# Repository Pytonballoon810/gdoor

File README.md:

<div align="center">

# GDoor

**Open hardware and firmware that connect a Gira door intercom to your smart home.**

Ring the doorbell, get a notification. Press a button in Home Assistant, the door opens.

&nbsp;

<sub>Left: the classic adapter (v3.1) &nbsp;·&nbsp; Right: the new DIN-rail board</sub>

</div>

---

## ✨ What it does

GDoor listens to and talks on the two-wire Gira door system bus. It is a DIY alternative to the
Gira TKS-IP-Gateway, built entirely from reverse-engineered findings about the bus.

<table>
<tr>
<td width="50%" valign="top">

### 🔔 Listen
Every bus message arrives in your smart home: doorbell presses, floor calls, the indoor
station picking up. Trigger a phone notification, a chime or a camera snapshot.

</td>
<td width="50%" valign="top">

### 🔓 Send
Put any message on the bus from an automation: open the door, switch the light, call a
station.

</td>
</tr>
<tr>
<td valign="top">

### 🏠 Integrate
[Home Assistant](https://gdoor-org.github.io/documentation/homeassistant.html) and
[openHAB](https://gdoor-org.github.io/documentation/openhab.html) through MQTT, or native
Home Assistant entities through the [ESPHome component](esphome/README.md).

</td>
<td valign="top">

### 🎙️ Talk *(in development)*
Two-way voice from the door station to Home Assistant over VoIP, on the boards with the
ES8374 audio codec. Video is neither supported nor planned.

</td>
</tr>
</table>

---

## 🧭 Two product lines

<table>
<tr>
<th width="50%">🔌 Classic adapter</th>
<th width="50%">🗄️ DIN-rail board</th>
</tr>
<tr>
<td valign="top">

A small shield that plugs onto an off-the-shelf ESP32 board. Cheap, proven, and powered by
the USB port of the ESP32 board.

- Versions **v3.0 → v4.1**
- Tagged releases with production files in [`hardware/releases/`](hardware/releases/README.md)
- **v3.1 / v3.1-1 is the version to build today**

</td>
<td valign="top">

One board with everything soldered on, in a 2-module (35 mm) DIN-rail housing that sits in
the distribution cabinet next to the intercom power supply.

- ESP32-S3, **wired Ethernet**, USB-C, audio codec
- 3D-printable enclosure, ESPHome configs ready
- **Designed, not built yet** — see [`DESIGN.md`](hardware/boards/din/DESIGN.md)

</td>
</tr>
</table>

---

## 📊 Version comparison

| | **v3.0** | **v3.1** | **v3.1-1** | **v4.0** | **v4.1** | **DIN** |
|---|:---:|:---:|:---:|:---:|:---:|:---:|
| **Status** | 🗄️ superseded | ✅ released | ✅ **recommended** | 🧪 prototype | 🚧 schematic only | 🚧 routed, not built |
| **Released** | Mar 2024 | May 2024 | Jun 2024 | Oct 2024 | — | — |
| **Form factor** | shield | shield | shield | shield | shield | DIN rail, 2 modules |
| **Microcontroller** | ESP32 D1 mini | ESP32 D1 mini | ESP32 D1 mini | ESP32 D1 mini | ESP32-S3 DevKitC‑1 (N8R2) | ESP32-S3-WROOM‑1 (N8R2), on board |
| **Bus receive** | wrong logic levels — needs a [bodge wire](https://github.com/gdoor-org/gdoor/blob/3.0/doc/pcb-modification.png) | LM393, adjustable threshold (DAC) | LM393, adjustable threshold (DAC) | fixed threshold | fixed threshold | fixed threshold |
| **Bus send (door opener)** | ✅ | ✅ | ✅ | ✅ | ✅ | ✅ |
| **Bus voltage measurement** | — | — | — | ✅ ÷9.2 | ✅ | ✅ ÷11, "bus connected" |
| **Audio codec (ES8374)** | — | — | — | ✅ hardware | ✅ hardware | ✅ hardware |
| **Two-way voice** | — | — | — | — | — | 🚧 ESPHome config, untested |
| **Network** | WiFi | WiFi | WiFi | WiFi | WiFi | **Ethernet** (W5500) or WiFi |
| **Ethernet add-on** | W5500 module wired on | W5500 module wired on | W5500 module wired on | ❌ pins taken by codec | — | built in, RJ45 |
| **Power** | ESP32 board USB | ESP32 board USB, filtered | ESP32 board USB, filtered | ESP32 board USB | DevKit USB | USB-C or 5 V terminal |
| **Bus connector** | screw terminal | pluggable terminal | pluggable, part swapped for JLC stock | pluggable terminal | pluggable terminal | pluggable 3.81 mm |
| **Status LEDs** | — | — | — | — | — | 2 |
| **Enclosure** | — | — | — | — | — | 3D-printed, TS35 clip |
| **MQTT firmware** | ✅ (RX on IO12/IO32) | ✅ | ✅ | ✅ bus only | — | ❌ |
| **ESPHome component** | ✅ | ✅ | ✅ | ✅ bus only | — | ✅ Ethernet · WiFi · voice |
| **Files** | [`v3.0/`](hardware/releases/v3.0) | [`v3.1/`](hardware/releases/v3.1) | [`v3.1-1/`](hardware/releases/v3.1-1) | [`v4.0/`](hardware/releases/v4.0) | [`esp32-mini/`](hardware/boards/esp32-mini) | [`din/`](hardware/boards/din) |

<sub>✅ supported &nbsp;·&nbsp; 🚧 in progress &nbsp;·&nbsp; 🧪 experimental &nbsp;·&nbsp; ❌ not possible &nbsp;·&nbsp; — not present.
The KiCad sources of each release are at the git tag of the same name (`3.0`, `3.1`, `3.1-1`, `4.0`).
v4.1's layout is still the v4.0 board.</sub>

### How the line evolved

```mermaid
timeline
    title GDoor hardware
    Mar 2024 : v3.0 : first adapter for the ESP32 D1 mini
    May 2024 : v3.1 : comparator with adjustable threshold, power filtering
    Jun 2024 : v3.1-1 : bus connector part swapped for JLCPCB stock
    Oct 2024 : v4.0 : first audio board, ES8374 codec, bus voltage
    Nov 2024 : v4.1 : moves to the ESP32-S3 (schematic)
    Oct 2026 : DIN : ESP32-S3, Ethernet, USB-C, audio, DIN-rail housing
```

---

## 🗄️ The DIN-rail board

<div align="center">

<sub>Click for the full video · interactive 3D viewer in [`showcase/`](hardware/boards/din/showcase/README.md)</sub>

</div>

<table>
<tr>
<td width="55%" valign="top">

| | |
|---|---|
| **MCU** | ESP32-S3-WROOM-1-N8R2 (8 MB flash, 2 MB PSRAM) |
| **Network** | W5500 + RJ45 with magnetics, or WiFi |
| **Audio** | ES8374 codec coupled to the bus |
| **Power** | 5 V from USB-C or screw terminal, OR-ed |
| **Front** | RJ45, USB-C, 2 status LEDs |
| **PCB** | 4 layers, 1.6 mm, ~85 × 50 mm |
| **Housing** | 35 mm wide, 90 mm high, TS35 clip |
| **Firmware** | ESPHome: [Ethernet](esphome/gdoor-din-ethernet.yaml) · [WiFi](esphome/gdoor-din-wifi.yaml) · [voice](esphome/gdoor-din-voice.yaml) |

</td>
<td width="45%" valign="top" align="center">

<sub>Printable base and lid — [`enclosure/`](hardware/boards/din/enclosure/README.md)</sub>

</td>
</tr>
</table>

| Where to look | |
|---|---|
| 📐 Design spec, pin map, open points | [`DESIGN.md`](hardware/boards/din/DESIGN.md) |
| 🏭 JLCPCB gerbers, BOM, CPL, iBOM | [`production/gdoor_din/`](hardware/boards/din/production/gdoor_din) |
| 📈 SPICE simulation of the bus front end and Ethernet | [`spice/`](hardware/boards/din/spice/README.md) |
| 🧊 Enclosure (OpenSCAD, STL, STEP) | [`enclosure/`](hardware/boards/din/enclosure/README.md) |

> [!NOTE]
> The DIN board is routed, DRC-clean and logic-checked, but **no board has been built or tested
> yet**. DIN releases are published from `din-*` git tags as GitHub releases.

---

## 🧩 Software

| | **MQTT firmware** | **ESPHome component** |
|---|---|---|
| **Folder** | [`firmware/`](firmware/README.md) | [`esphome/`](esphome/README.md) |
| **Talks to** | any MQTT broker → Home Assistant, openHAB, Node-RED … | Home Assistant native API |
| **Install** | [web installer](https://gdoor-org.github.io/documentation/firmware.html), no toolchain | your ESPHome YAML, `external_components` |
| **Setup** | web page on the adapter, web console for live bus traffic | YAML; learning mode logs the bus |
| **Boards** | classic adapter v3.x, v4.0 | classic adapter v3.x, v4.0, DIN board |
| **Extras** | Ethernet via W5500 add-on | Ethernet, other ESPHome components alongside (e.g. Bluetooth proxy), voice on DIN |

Both build the **same bus encoder/decoder**: the ESPHome component carries a copy of
`firmware/src`, kept in sync by `tools/sync_esphome_core.py` and checked in CI.

---

## 📁 Repository layout

| Folder | Contents |
|---|---|
| [`firmware/`](firmware/README.md) | Arduino/PlatformIO firmware (MQTT, web installer, web console) |
| [`esphome/`](esphome/README.md) | ESPHome external component and the DIN board configs |
| [`hardware/`](hardware/README.md) | KiCad boards (`boards/esp32-mini`, `boards/din`), shared library (`lib/`), release files (`releases/`) |
| [`software/bus-debugger/`](software/bus-debugger/README.md) | MQTT bus listener for decoding messages |
| `tools/` | Repository helper scripts |

---

## 🤝 Contributing

GDoor collects and documents what is known about the Gira door system, all figured out by
reverse engineering. Bus captures from installations we have not seen yet, bug reports, and
hardware tests are all welcome — open an issue or a pull request.

<div align="center">

<sub>Licensed under the [GNU GPL v3](LICENSE) · not affiliated with Gira</sub>

</div>

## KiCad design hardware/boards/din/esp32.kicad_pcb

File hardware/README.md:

# Hardware

More information about the hardware is on the
[GDoor Homepage](https://gdoor-org.github.io/documentation/firmware.html).

| Folder | Contents |
|---|---|
| `boards/esp32-mini/` | The GDoor adapter (KiCad). The schematic is V4.1 (ESP32-S3, work in progress); the layout is still the V4.0 board. |
| `boards/din/` | DIN-rail board with Ethernet and audio, plus its 3D-printed enclosure. See [`DESIGN.md`](boards/din/DESIGN.md). |
| `lib/` | KiCad footprints (`Library.pretty`) and symbols (`symbols.kicad_sym`) shared by both boards. |
| `releases/` | Production files of every released adapter version, see [`releases/README.md`](releases/README.md). |

Older board sources are not kept as folders; check out the git tag of a release
(`3.0`, `3.1`, `3.1-1`, `4.0`) to open that version in KiCad.

Each board keeps its own `3dmodels/`, because the boards store the model paths
relative to their project folder.

## DIN board in action

Click the preview for the full video. The interactive 3D version is in
[`boards/din/showcase/`](boards/din/showcase/README.md).

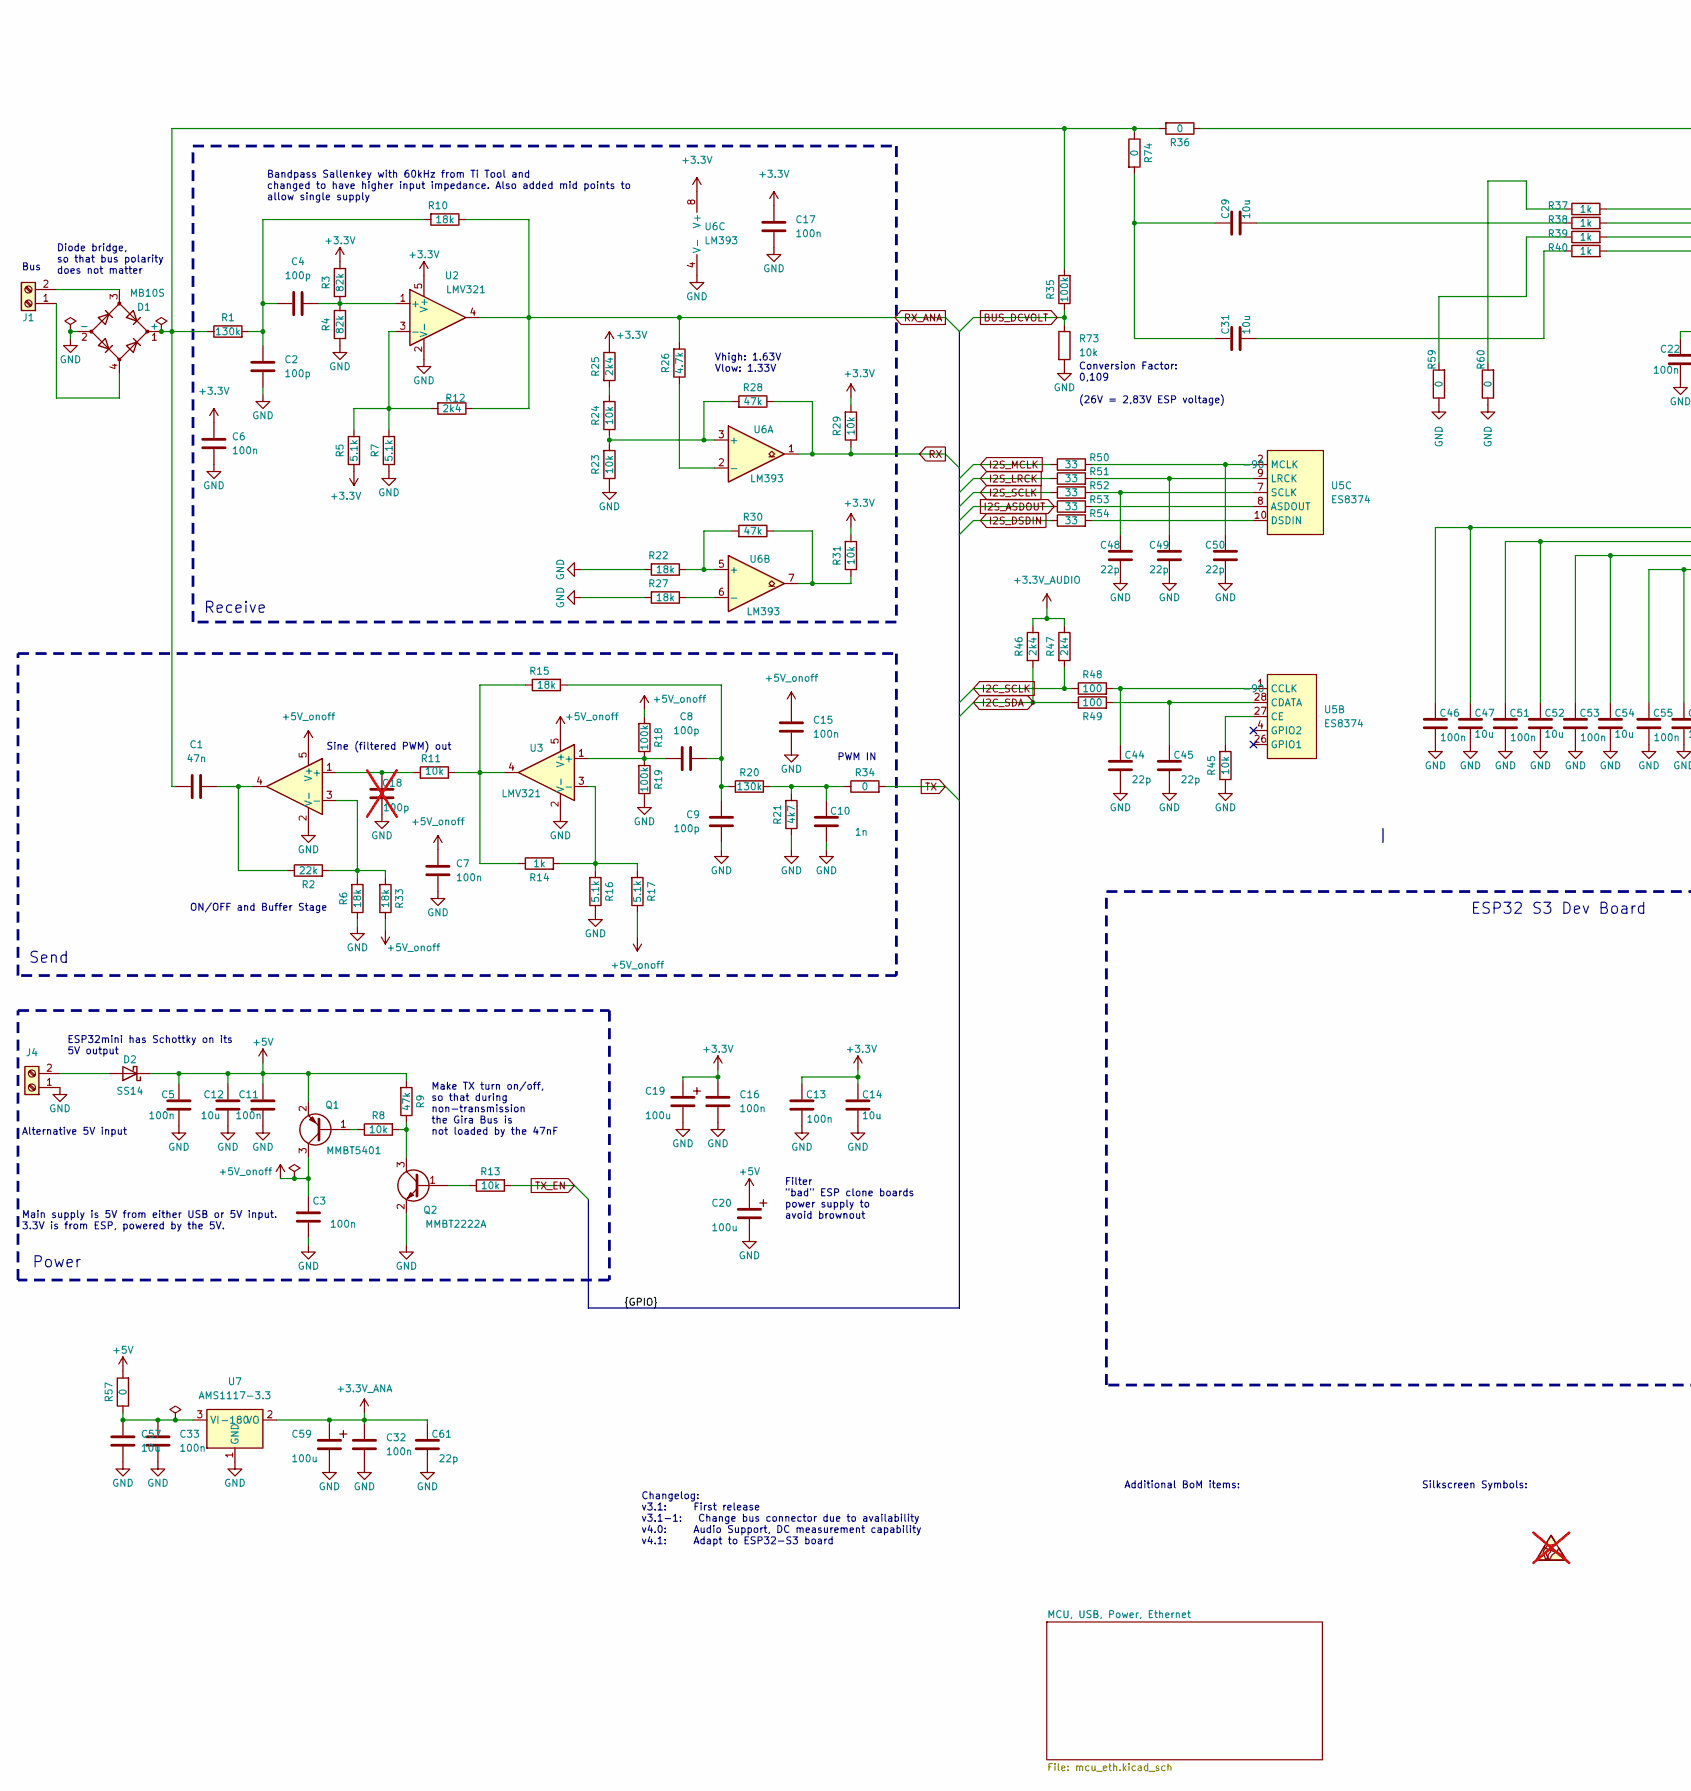
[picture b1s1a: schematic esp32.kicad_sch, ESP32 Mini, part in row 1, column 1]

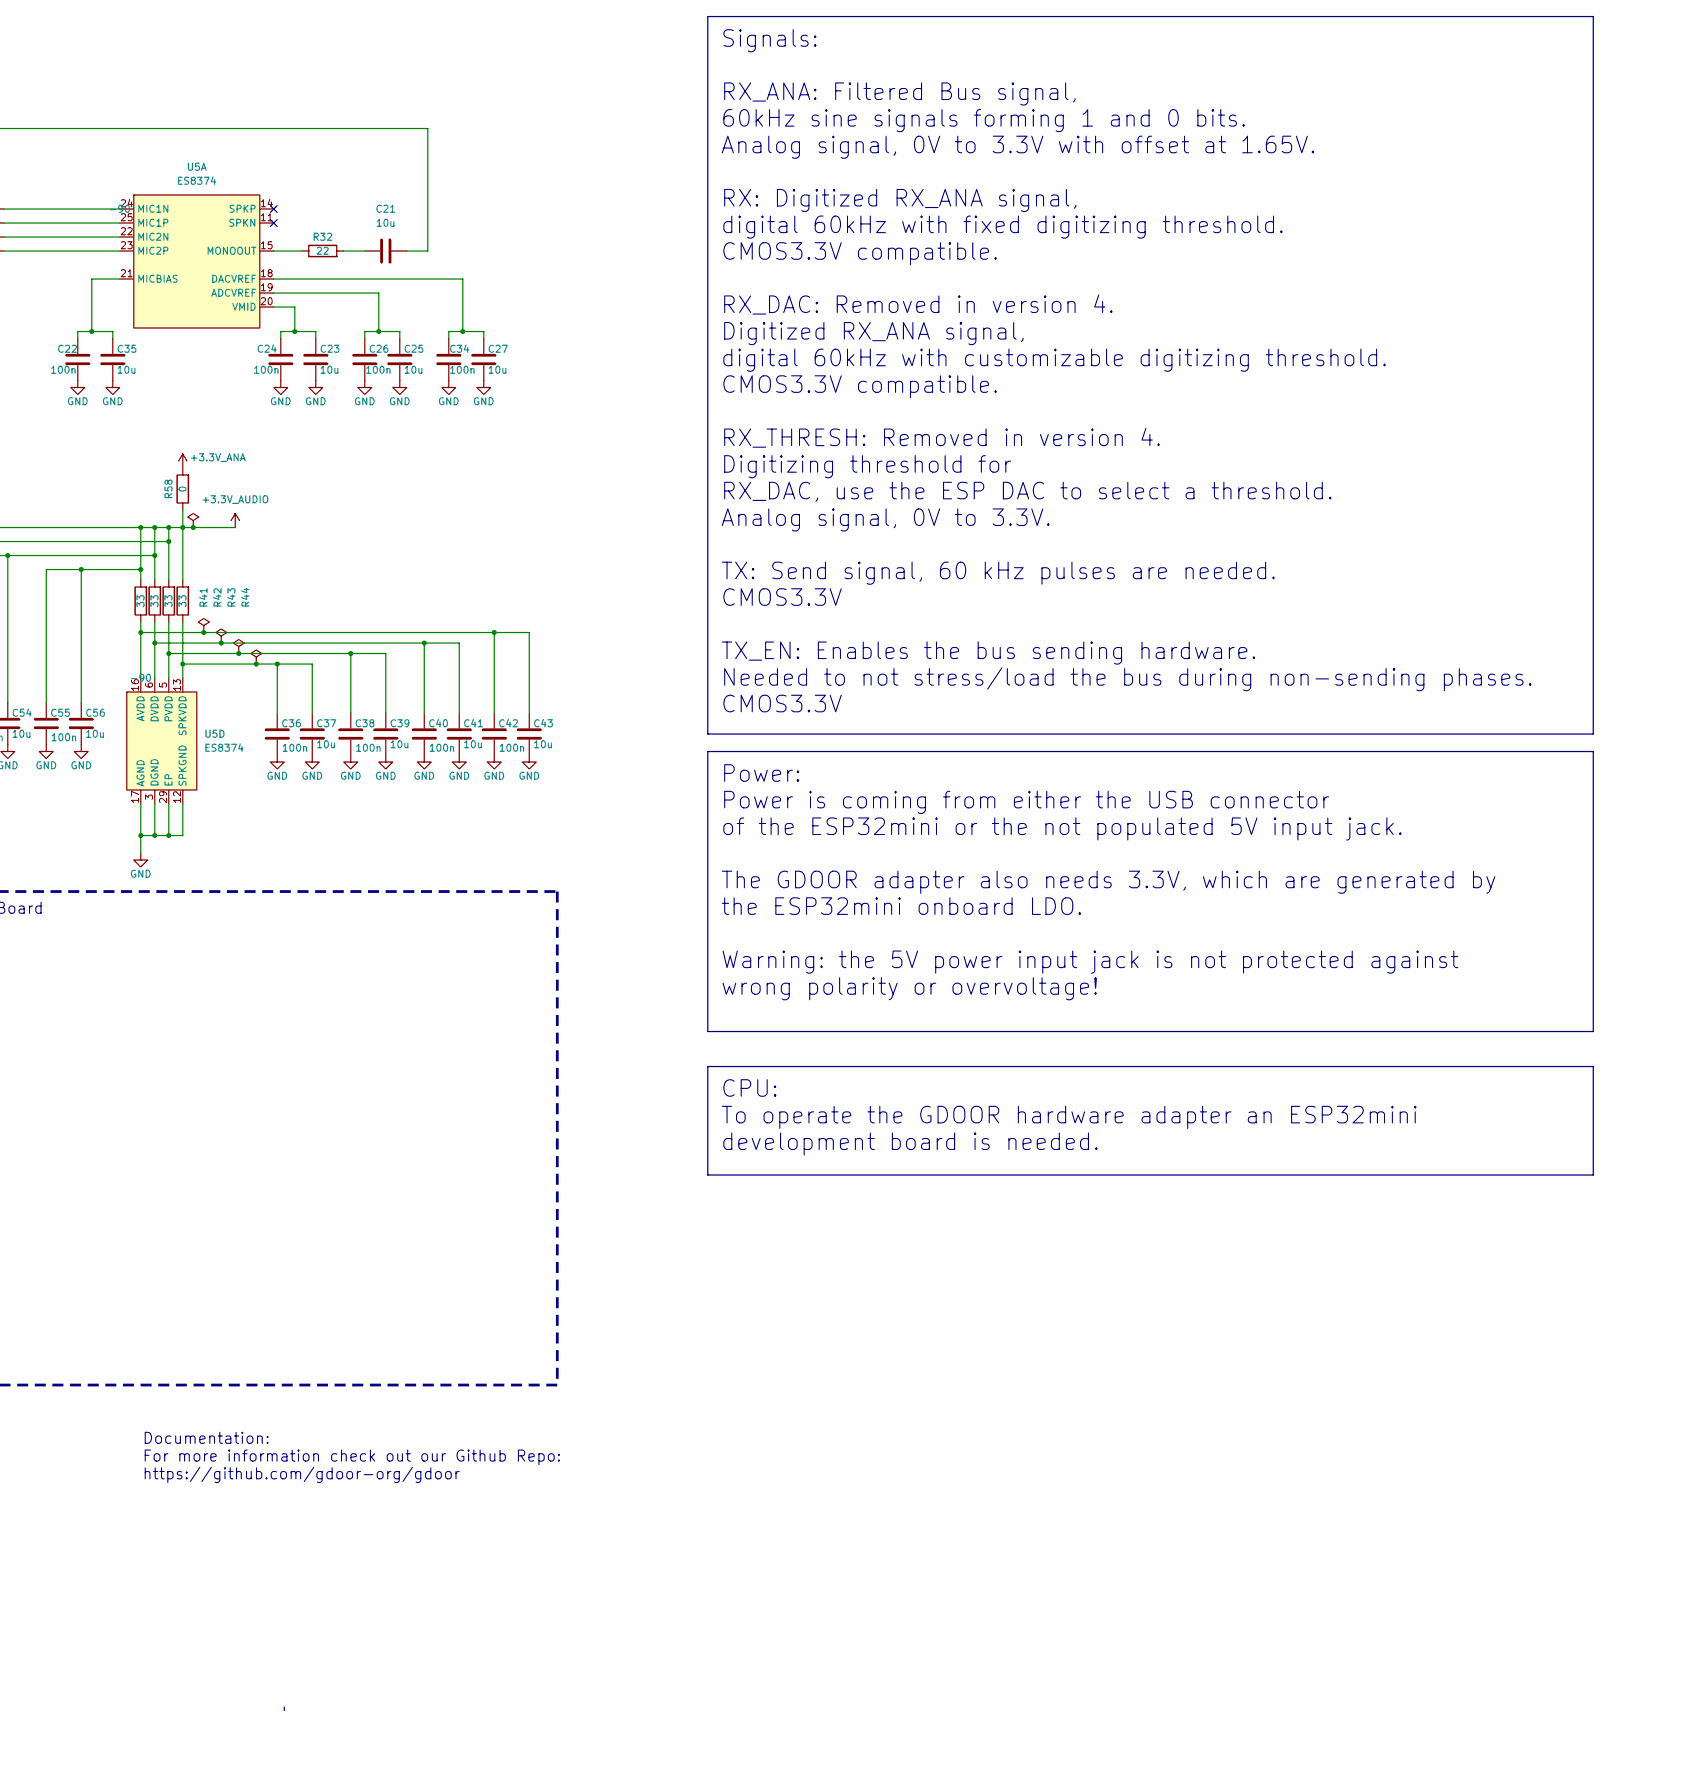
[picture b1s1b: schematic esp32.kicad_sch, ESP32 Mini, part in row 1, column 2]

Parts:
C1: 47n; C_0603_1608Metric_Pad1.08x0.95mm_HandSolder; MPN C1622
C2, C4, C8, C9: 100p; C_0402_1005Metric_Pad0.74x0.62mm_HandSolder; MPN C1546
C3, C5, C6, C7, C11, C13, C15, C16, C17, C36, C38, C40, C42, C46, C51, C53, C55: 100n; C_0402_1005Metric_Pad0.74x0.62mm_HandSolder; MPN C307331
C10: 1n; C_0402_1005Metric_Pad0.74x0.62mm_HandSolder; MPN C1523
C12: 10u; C_0603_1608Metric_Pad1.08x0.95mm_HandSolder; MPN C96446
C14, C23, C25, C27, C35, C37, C39, C41, C43, C47, C52, C54, C56: 10u; C_0402_1005Metric_Pad0.74x0.62mm_HandSolder; MPN C15525
C18: 100p; C_0402_1005Metric_Pad0.74x0.62mm_HandSolder; MPN C1546; not fitted
C19, C20, C59: 100u; C_1210_3225Metric_Pad1.33x2.70mm_HandSolder; MPN C23742
C21, C57: 10u; C_1206_3216Metric_Pad1.33x1.80mm_HandSolder; MPN C13585
C22, C24, C26, C32, C33, C34: 100n; C_0402_1005Metric_Pad0.74x0.62mm_HandSolder; MPN C1525
C29: 10u; C_1206_3216Metric; MPN C13585
C31: 10u; C_0805_2012Metric; MPN C440198
C44, C45, C48, C49, C50, C61: 22p; C_0402_1005Metric_Pad0.74x0.62mm_HandSolder; MPN C1555
D1: MB10S; SOIC-4_4.55x3.7mm_P2.54mm; MPN C2488
D2: SS14; D_SMA; MPN C2480
J1: PlugIn_Terminal_Screw; anschlussklemme2x1_3_5; MPN C695629; JLCPCB Rotation Offset 90
J4: 5V_IN; anschlussklemme2x1_3_5; MPN C695629; JLCPCB Rotation Offset 90
Q1: MMBT5401; SOT-23; MPN C8326
Q2: MMBT2222A; SOT-23; MPN C8512
R1, R20: 130k; R_0603_1608Metric; MPN C22795
R2: 22k; R_0402_1005Metric_Pad0.72x0.64mm_HandSolder; MPN C25768
R3, R4: 82k; R_0603_1608Metric; MPN C23254
R5, R7, R16, R17: 5.1k; R_0402_1005Metric_Pad0.72x0.64mm_HandSolder; MPN C25905
R6, R10, R15, R22, R27, R33: 18k; R_0402_1005Metric_Pad0.72x0.64mm_HandSolder; MPN C25762
R8, R11, R13, R23, R24, R29, R31, R45, R73: 10k; R_0402_1005Metric_Pad0.72x0.64mm_HandSolder; MPN C25744
R9, R28, R30: 47k; R_0402_1005Metric_Pad0.72x0.64mm_HandSolder; MPN C25792
R12, R25, R46, R47: 2k4; R_0402_1005Metric_Pad0.72x0.64mm_HandSolder; MPN C25882
R14, R37, R38, R39, R40: 1k; R_0402_1005Metric_Pad0.72x0.64mm_HandSolder; MPN C11702
R18, R19, R35: 100k; R_0402_1005Metric_Pad0.72x0.64mm_HandSolder; MPN C25741
R21: 4k7; R_0402_1005Metric_Pad0.72x0.64mm_HandSolder; MPN C25900
R26: 4.7k; R_0402_1005Metric_Pad0.72x0.64mm_HandSolder; MPN C25900
R32: 22; R_0402_1005Metric_Pad0.72x0.64mm_HandSolder; MPN C25092
R34, R36, R57, R58, R59, R60, R74: 0; R_0402_1005Metric_Pad0.72x0.64mm_HandSolder; MPN C17168
R41, R42, R43, R44, R50, R51, R52, R53, R54: 33; R_0402_1005Metric_Pad0.72x0.64mm_HandSolder; MPN C25105
R48, R49: 100; R_0402_1005Metric_Pad0.72x0.64mm_HandSolder; MPN C25076
S1: SYM_ESD_Small; ESD-Logo_6.6x6mm_SilkScreen; not fitted
U1: TLV9351; SOT-353_SC-70-5; MPN C4367425; JLCPCB Rotation Offset 180
U2, U3: LMV321; SOT-23-5; MPN C7972
U5: ES8374; QFN-28-1EP_4x4mm_P0.45mm_EP2.4x2.4mm; MPN C365738; JlcRotOffset -90
U6: LM393; SOIC-8_3.9x4.9mm_P1.27mm; MPN C7955; JlcRotOffset -90
U7: AMS1117-3.3; SOT-223-3_TabPin2; MPN C6186; JlcRotOffset -180

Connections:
+3.3V: C6.1, C13.2, C14.2, C16.1, C17.1, C19.1, R3.2, R5.1, R25.1, R29.2, R31.2, U2.5 (V+), U6.8 (V+); also elsewhere on the board
+3.3V_ANA: C32.1, C59.1, C61.2, R58.2, U7.2 (VO)
+3.3V_AUDIO: C46.2, C47.2, C51.2, C52.2, C53.2, C54.2, C55.2, C56.2, R41.2, R42.2, R43.2, R44.2, R46.1, R47.1, R58.1
+5V: C5.1, C11.2, C12.2, C20.1, D2.1 (K), Q1.2 (E1), R9.2, R57.2; also elsewhere on the board
+5V_onoff: C3.1, C7.1, C15.1, Q1.3 (C1), R17.1, R18.2, R33.1, U1.5 (V+), U3.5 (V+)
BUS_DCVOLT: R35.1, R73.1; also elsewhere on the board
GND: C2.1, C3.2, C5.2, C6.2, C7.2, C9.1, C10.1, C11.1, C12.1, C13.1, C14.1, C15.2, C16.2, C17.2, C18.1, C19.2, C20.2, C22.2, C23.1, C24.2, C25.1, C26.2, C27.1, C32.2, C33.2, C34.2, C35.1, C36.1, C37.1, C38.1, C39.1, C40.1, C41.1, C42.1, C43.1, C44.1, C45.1, C46.1, C47.1, C48.1, C49.1, C50.1, C51.1, C52.1, C53.1, C54.1, C55.1, C56.1, C57.1, C59.2, C61.1, D1.2 (-), J4.1, Q2.2 (E), R4.1, R6.1, R7.1, R16.1, R19.1, R21.1, R22.2, R23.1, R27.2, R45.1, R59.1, R60.1, R73.2, U1.2 (V-), U2.2 (V-), U3.2 (V-), U5.3 (DGND), U5.12 (SPKGND), U5.17 (AGND), U5.29 (EP), U6.4 (V-), U7.1 (GND); also elsewhere on the board
I2C_SCLK: R47.2, R48.1; also elsewhere on the board
I2C_SDA: R46.2, R49.1; also elsewhere on the board
I2S_ASDOUT: R53.1; also elsewhere on the board
I2S_DSDIN: R54.1; also elsewhere on the board
I2S_LRCK: R51.1; also elsewhere on the board
I2S_MCLK: R50.1; also elsewhere on the board
I2S_SCLK: R52.1; also elsewhere on the board
unnamed: C1.1, R2.1, U1.4
unnamed: C2.2, C4.2, R1.2, R10.2
unnamed: C8.2, C9.2, R15.2, R20.2
unnamed: C10.2, R20.1, R21.2, R34.1
unnamed: C21.1, R32.2
unnamed: C21.2, R36.1
unnamed: C29.1, R38.1
unnamed: C29.2, C31.2, R74.2
unnamed: C31.1, R40.1
unnamed: C1.2, D1.1 (+), R1.1, R35.2, R36.2, R74.1
unnamed: D2.2 (A), J4.2
unnamed: D1.4, J1.1
unnamed: D1.3, J1.2
unnamed: Q1.1 (B1), R8.1
unnamed: Q2.1 (B), R13.1
unnamed: Q2.3 (C), R8.2, R9.1
unnamed: R11.1, R14.1, R15.1, U3.4
unnamed: R24.2, R25.2
unnamed: R30.1, R31.1, U6.7
unnamed: R37.1, R60.2
unnamed: R39.1, R59.2
unnamed: C18.2, R11.2, U1.1 (+)
unnamed: R2.2, R6.2, R33.2, U1.3 (-)
unnamed: C4.1, R3.1, R4.2, U2.1 (+)
unnamed: R5.2, R7.2, R12.2, U2.3 (-)
unnamed: C8.1, R18.1, R19.2, U3.1 (+)
unnamed: R14.2, R16.2, R17.2, U3.3 (-)
unnamed: C25.2, C26.1, U5.19 (ADCVREF)
unnamed: C27.2, C34.1, U5.18 (DACVREF)
unnamed: R37.2, U5.24 (MIC1N)
unnamed: R38.2, U5.25 (MIC1P)
unnamed: R39.2, U5.22 (MIC2N)
unnamed: R40.2, U5.23 (MIC2P)
unnamed: C22.1, C35.2, U5.21 (MICBIAS)
unnamed: R32.1, U5.15 (MONOOUT)
unnamed: C23.2, C24.1, U5.20 (VMID)
unnamed: C44.2, R48.2, U5.1 (CCLK)
unnamed: C45.2, R49.2, U5.28 (CDATA)
unnamed: R45.2, U5.27 (CE)
unnamed: R53.2, U5.8 (ASDOUT)
unnamed: R54.2, U5.10 (DSDIN)
unnamed: C49.2, R51.2, U5.9 (LRCK)
unnamed: C50.2, R50.2, U5.2 (MCLK)
unnamed: C48.2, R52.2, U5.7 (SCLK)
unnamed: C42.2, C43.2, R41.1, U5.16 (AVDD)
unnamed: C40.2, C41.2, R42.1, U5.6 (DVDD)
unnamed: C38.2, C39.2, R43.1, U5.5 (PVDD)
unnamed: C36.2, C37.2, R44.1, U5.13 (SPKVDD)
unnamed: R23.2, R24.1, R28.2, U6.3 (+)
unnamed: R26.1, U6.2 (-)
unnamed: R22.1, R30.2, U6.5 (+)
unnamed: R27.1, U6.6 (-)
unnamed: C33.1, C57.2, R57.1, U7.3 (VI)
RX: R28.1, R29.1, U6.1; also elsewhere on the board
RX_ANA: R10.1, R12.1, R26.2, U2.4; also elsewhere on the board
TX: R34.2; also elsewhere on the board
TX_EN: R13.2; also elsewhere on the board

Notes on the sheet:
Sine (filtered PWM) out
Make TX turn on/off, so that during non-transmission the Gira Bus is not loaded by the 47nF
Vhigh: 1.63V Vlow: 1.33V
Bandpass Sallenkey with 60kHz from Ti Tool and changed to have higher input impedance. Also added mid points to allow single supply
Additional BoM items:
Silkscreen Symbols:
Power
ESP32mini has Schottky on its 5V output
Filter "bad" ESP clone boards power supply to avoid brownout
Receive
PWM IN
Diode bridge, so that bus polarity does not matter
Main supply is 5V from either USB or 5V input. 3.3V is from ESP, powered by the 5V.
Alternative 5V input
ON/OFF and Buffer Stage
Changelog: v3.1: First release v3.1-1: Change bus connector due to availability v4.0: Audio Support, DC measurement capability v4.1: Adapt to ESP32-S3 board
Conversion Factor: 0,109 (26V = 2,83V ESP voltage)
Bus
Send
ESP32 S3 Dev Board
Power: Power is coming from either the USB connector of the ESP32mini or the not populated 5V input jack. The GDOOR adapter also needs 3.3V, which are generated by the ESP32mini onboard LDO. Warning: the 5V power input jack is not protected against wrong polarity or overvoltage!
CPU: To operate the GDOOR hardware adapter an ESP32mini development board is needed.
Documentation: For more information check out our Github Repo: https://github.com/gdoor-org/gdoor
Signals: RX_ANA: Filtered Bus signal, 60kHz sine signals forming 1 and 0 bits. Analog signal, 0V to 3.3V with offset at 1.65V. RX: Digitized RX_ANA signal, digital 60kHz with fixed digitizing threshold. CMOS3.3V compatible. RX_DAC: Removed in version 4. Digitized RX_ANA signal, digital 60kHz with c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

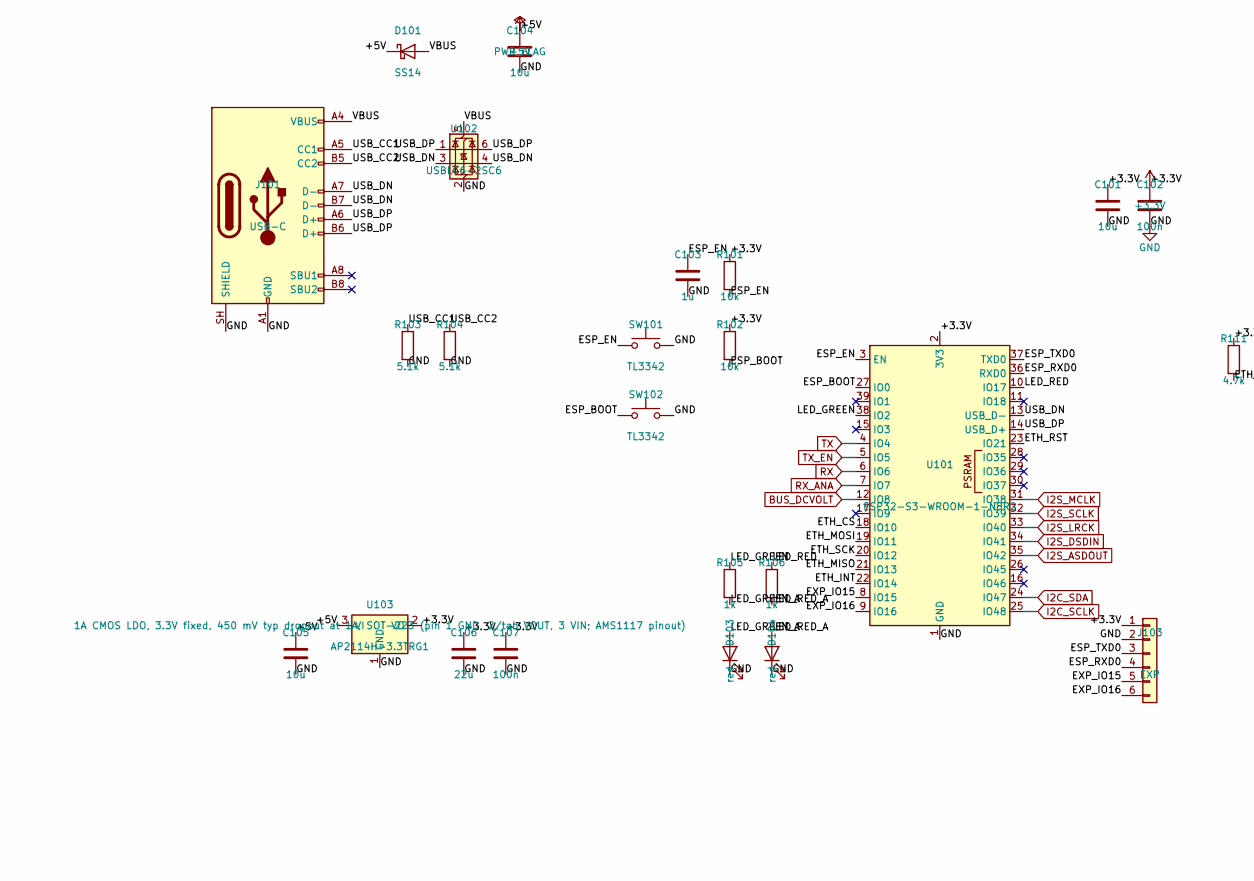
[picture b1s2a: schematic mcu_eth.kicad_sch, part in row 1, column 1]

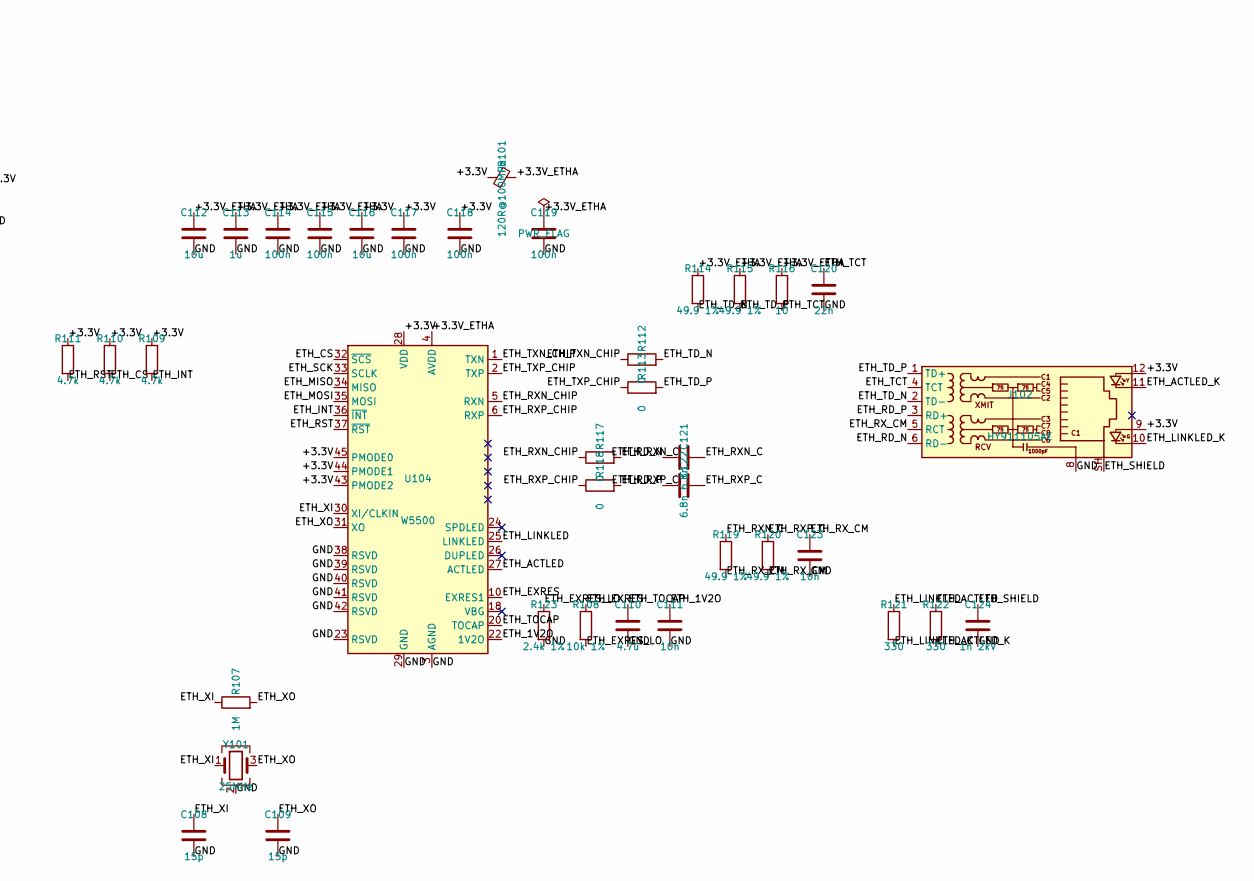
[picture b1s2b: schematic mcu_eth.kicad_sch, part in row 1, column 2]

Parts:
C101, C104, C105, C112, C116: 10u; C_0603_1608Metric; LCSC C19702
C102, C107, C114, C115, C117, C118, C119: 100n; C_0402_1005Metric; LCSC C1525
C103, C113: 1u; C_0402_1005Metric; LCSC C52923
C106: 22u; C_0805_2012Metric; LCSC C45783
C108, C109: 15p; C_0402_1005Metric; LCSC C1548
C110: 4.7u; C_0603_1608Metric; LCSC C19666
C111, C123: 10n; C_0402_1005Metric; LCSC C15195
C120: 22n; C_0402_1005Metric; LCSC C1532
C121, C122: 6.8n; C_0402_1005Metric; LCSC C1542
C124: 1n 2kV; C_1206_3216Metric; LCSC C9196
D101: SS14; D_SMA; LCSC C2480
D103, D104: red; LED_0603_1608Metric; LCSC C2286
FB101: 120R@100MHz; L_0603_1608Metric; LCSC C14709
J101: USB-C; USB_C_Receptacle_HRO_TYPE-C-31-M-12; LCSC C165948
J102: HY911105AE; RJ45_Hanrun_HR911105A_Horizontal; LCSC C69427
J103: EXP; PinHeader_1x06_P2.54mm_Vertical; LCSC C37208
R101, R102: 10k; R_0402_1005Metric; LCSC C25744
R103, R104: 5.1k; R_0402_1005Metric; LCSC C25905
R105, R106: 1k; R_0402_1005Metric; LCSC C11702
R107: 1M; R_0402_1005Metric; LCSC C26083
R108: 10k 1%; R_0402_1005Metric; LCSC C25744
R109, R110, R111: 4.7k; R_0402_1005Metric; LCSC C25900
R112, R113, R117, R118: 0; R_0402_1005Metric; LCSC C17168
R114, R115, R119, R120: 49.9 1%; R_0402_1005Metric; LCSC C25120
R116: 10; R_0402_1005Metric; LCSC C25077
R121, R122: 330; R_0402_1005Metric; LCSC C25104
R123: 2.4k 1%; R_0402_1005Metric; LCSC C25882
SW101, SW102: TL3342; SW_SPST_TL3342; LCSC C318884
U101: ESP32-S3-WROOM-1-N8R2; ESP32-S3-WROOM-1; LCSC C2913204
U102: USBLC6-2SC6; SOT-23-6; LCSC C2687116
U103: AP2114H-3.3TRG1; SOT-223-3_TabPin2; LCSC C150716
U104: W5500; LQFP-48_7x7mm_P0.5mm; LCSC C32843
Y101: 25MHz; Crystal_SMD_3225-4Pin_3.2x2.5mm; LCSC C9006

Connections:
+3.3V: C101.1, C102.1, C106.1, C107.1, C116.1, C117.1, C118.1, FB101.1, J102.9, J102.12, J103.1, R101.1, R102.1, R109.1, R110.1, R111.1, U101.2 (3V3), U103.2 (VO), U104.28 (VDD), U104.43 (PMODE2), U104.44 (PMODE1), U104.45 (PMODE0); also elsewhere on the board
+5V: C104.1, C105.1, D101.1 (K), U103.3 (VI); also elsewhere on the board
/MCU, USB, Power, Ethernet/+3.3V_ETHA: C112.1, C113.1, C114.1, C115.1, C119.1, FB101.2, R114.1, R115.1, R116.1, U104.4 (AVDD), U104.8 (AVDD), U104.11 (AVDD), U104.15 (AVDD), U104.17 (AVDD), U104.21 (AVDD)
/MCU, USB, Power, Ethernet/ESP_BOOT: R102.2, SW102.1, U101.27 (IO0)
/MCU, USB, Power, Ethernet/ESP_EN: C103.1, R101.2, SW101.1, U101.3 (EN)
/MCU, USB, Power, Ethernet/ESP_RXD0: J103.4, U101.36 (RXD0)
/MCU, USB, Power, Ethernet/ESP_TXD0: J103.3, U101.37 (TXD0)
/MCU, USB, Power, Ethernet/ETH_1V2O: C111.1, U104.22 (1V2O)
/MCU, USB, Power, Ethernet/ETH_ACTLED: R122.1, U104.27 (ACTLED)
/MCU, USB, Power, Ethernet/ETH_ACTLED_K: J102.11, R122.2
/MCU, USB, Power, Ethernet/ETH_CS: R110.2, U101.18 (IO10), U104.32 (~SCS)
/MCU, USB, Power, Ethernet/ETH_EXRES: R108.1, U104.10 (EXRES1)
/MCU, USB, Power, Ethernet/ETH_EXRES_LO: R108.2, R123.1
/MCU, USB, Power, Ethernet/ETH_INT: R109.2, U101.22 (IO14), U104.36 (~INT)
/MCU, USB, Power, Ethernet/ETH_LINKLED: R121.1, U104.25 (LINKLED)
/MCU, USB, Power, Ethernet/ETH_LINKLED_K: J102.10, R121.2
/MCU, USB, Power, Ethernet/ETH_MISO: U101.21 (IO13), U104.34 (MISO)
/MCU, USB, Power, Ethernet/ETH_MOSI: U101.19 (IO11), U104.35 (MOSI)
/MCU, USB, Power, Ethernet/ETH_RD_N: C121.1, J102.6 (RD-)
/MCU, USB, Power, Ethernet/ETH_RD_P: C122.1, J102.3 (RD+)
/MCU, USB, Power, Ethernet/ETH_RST: R111.2, U101.23 (IO21), U104.37 (~RST)
/MCU, USB, Power, Ethernet/ETH_RXN_C: C121.2, R117.2, R119.1
/MCU, USB, Power, Ethernet/ETH_RXN_CHIP: R117.1, U104.5 (RXN)
/MCU, USB, Power, Ethernet/ETH_RXP_C: C122.2, R118.2, R120.1
/MCU, USB, Power, Ethernet/ETH_RXP_CHIP: R118.1, U104.6 (RXP)
/MCU, USB, Power, Ethernet/ETH_RX_CM: C123.1, J102.5 (RCT), R119.2, R120.2
/MCU, USB, Power, Ethernet/ETH_SCK: U101.20 (IO12), U104.33 (SCLK)
/MCU, USB, Power, Ethernet/ETH_SHIELD: C124.1, J102.SH
/MCU, USB, Power, Ethernet/ETH_TCT: C120.1, J102.4 (TCT), R116.2
/MCU, USB, Power, Ethernet/ETH_TD_N: J102.2 (TD-), R112.2, R114.2
/MCU, USB, Power, Ethernet/ETH_TD_P: J102.1 (TD+), R113.2, R115.2
/MCU, USB, Power, Ethernet/ETH_TOCAP: C110.1, U104.20 (TOCAP)
/MCU, USB, Power, Ethernet/ETH_TXN_CHIP: R112.1, U104.1 (TXN)
/MCU, USB, Power, Ethernet/ETH_TXP_CHIP: R113.1, U104.2 (TXP)
/MCU, USB, Power, Ethernet/ETH_XI: C108.1, R107.1, U104.30 (XI/CLKIN), Y101.1
/MCU, USB, Power, Ethernet/ETH_XO: C109.1, R107.2, U104.31 (XO), Y101.3
/MCU, USB, Power, Ethernet/EXP_IO15: J103.5, U101.8 (IO15)
/MCU, USB, Power, Ethernet/EXP_IO16: J103.6, U101.9 (IO16)
/MCU, USB, Power, Ethernet/LED_GREEN: R105.1, U101.38 (IO2)
/MCU, USB, Power, Ethernet/LED_GREEN_A: D103.2 (A), R105.2
/MCU, USB, Power, Ethernet/LED_RED: R106.1, U101.10 (IO17)
/MCU, USB, Power, Ethernet/LED_RED_A: D104.2 (A), R106.2
/MCU, USB, Power, Ethernet/USB_CC1: J101.A5 (CC1), R103.1
/MCU, USB, Power, Ethernet/USB_CC2: J101.B5 (CC2), R104.1
/MCU, USB, Power, Ethernet/USB_DN: J101.A7 (D-), J101.B7 (D-), U101.13 (USB_D-), U102.3 (I/O2), U102.4 (I/O2)
/MCU, USB, Power, Ethernet/USB_DP: J101.A6 (D+), J101.B6 (D+), U101.14 (USB_D+), U102.1 (I/O1), U102.6 (I/O1)
/MCU, USB, Power, Ethernet/VBUS: D101.2 (A), J101.A4 (VBUS), J101.A9 (VBUS), J101.B4 (VBUS), J101.B9 (VBUS), U102.5 (VBUS)
BUS_DCVOLT: U101.12 (IO8); also elsewhere on the board
GND: C101.2, C102.2, C103.2, C104.2, C105.2, C106.2, C107.2, C108.2, C109.2, C110.2, C111.2, C112.2, C113.2, C114.2, C115.2, C116.2, C117.2, C118.2, C119.2, C120.2, C123.2, C124.2, D103.1 (K), D104.1 (K), J101.A1 (GND), J101.A12 (GND), J101.B1 (GND), J101.B12 (GND), J101.SH (SHIELD), J102.8, J103.2, R103.2, R104.2, R123.2, SW101.2, SW102.2, U101.1 (GND), U101.40 (GND), U101.41 (GND), U102.2 (GND), U103.1 (GND), U104.3 (AGND), U104.9 (AGND), U104.14 (AGND), U104.16 (AGND), U104.19 (AGND), U104.23 (RSVD), U104.29 (GND), U104.38 (RSVD), U104.39 (RSVD), U104.40 (RSVD), U104.41 (RSVD), U104.42 (RSVD), U104.48 (AGND), Y101.2 (G), Y101.4 (G); also elsewhere on the board
I2C_SCLK: U101.25 (IO48); also elsewhere on the board
I2C_SDA: U101.24 (IO47); also elsewhere on the board
I2S_ASDOUT: U101.35 (IO42); also elsewhere on the board
I2S_DSDIN: U101.34 (IO41); also elsewhere on the board
I2S_LRCK: U101.33 (IO40); also elsewhere on the board
I2S_MCLK: U101.31 (IO38); also elsewhere on the board
I2S_SCLK: U101.32 (IO39); also elsewhere on the board
RX: U101.6 (IO6); also elsewhere on the board
RX_ANA: U101.7 (IO7); also elsewhere on the board
TX: U101.4 (IO4); also elsewhere on the board
TX_EN: U101.5 (IO5); also elsewhere on the board

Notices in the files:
README.md:
License: GPL-3.0
